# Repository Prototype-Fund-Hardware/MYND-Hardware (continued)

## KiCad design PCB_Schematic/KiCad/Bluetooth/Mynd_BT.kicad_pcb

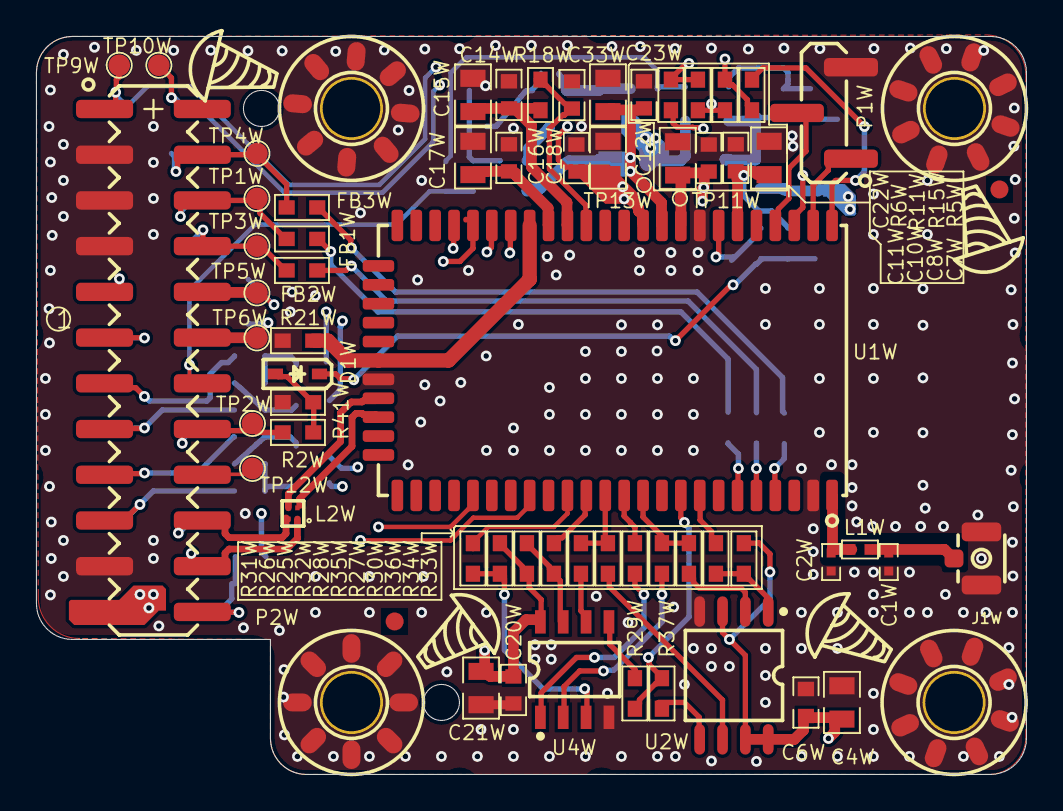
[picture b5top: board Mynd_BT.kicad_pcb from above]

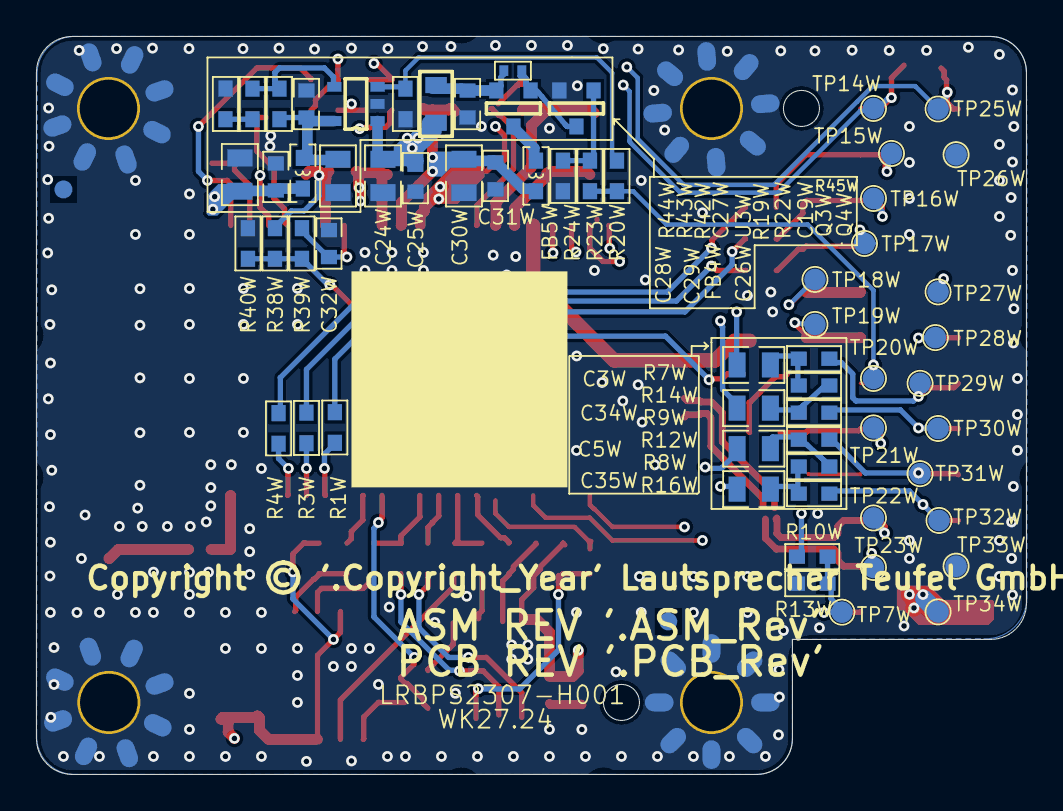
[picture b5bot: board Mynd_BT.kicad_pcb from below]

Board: 4 copper layers, 55.0 x 41.0 mm, 136 parts (66 on the bottom side), 79 nets.

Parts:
C1W, C2W: 0.5pF; C0402
C3W, C4W, C5W, C7W, C11W, C12W, C15W, C17W, C21W, C23W, C24W, C26W, C28W, C30W, C34W, C35W: 10uF; C0805_145
C6W, C8W, C10W, C14W, C16W, C18W, C19W, C20W, C22W, C25W, C27W, C29W, C31W: 100nF; C0603X100
C32W: 100pF; C0603X80
C33W: 1nF; C0603X100
D1W: 1N4148; SOD-323
FB1W, FB2W, FB3W: 0R; R0603
FB4W, FB5W: 600R; L0603
J1W: 9181-000030; I-PEX MHF
L1W: 0R; R0402
L2W: 90R; COM_CHOKE_SMD_ICMF062P
MH1W, MH2W, MH3W, MH4W: SCREW_HOLE; SCREW_D32
MK1W, MK2W: MARK
P1W: Header 3P PITCH=2.54mm SMT; Pin_Header_SMD_S_T_254_3P
P2W: Connector 2 x 12P 2.54mm SMT; Pin_Header_SMD_2X12_254
Q3W: CJ3401; SOT23-GSD
Q4W: 2N7002K; SOT23-GSD
R1W, R3W, R4W, R27W, R28W, R29W, R30W, R31W, R32W, R34W, R35W, R36W, R37W: 33R; R0603
R2W, R11W, R13W, R15W, R25W, R26W, R33W: 10k; R0603
R5W, R6W, R9W, R16W, R21W: 0R; R0603
R7W, R12W: 3.3k; R0603
R8W, R14W: 6.8k; R0603
R10W: 100k; R0603
R18W: 33k; R0603
R19W, R24W, R41W: 47k; R0603
R20W, R23W, R39W: 1k; R0603
R22W: 2.2R; R0805
R38W: 1M; R0603
R40W: 560k; R0603
R42W: 680k; R0603
R43W: 150k; R0603
R44W: 20k; R0603
R45W: 100k; R0402
TP1W, TP2W, TP3W, TP4W, TP5W, TP6W, TP7W, TP9W, TP10W, TP12W, TP14W, TP15W, TP16W, TP17W, TP18W, TP19W, TP20W, TP21W, TP22W, TP23W, TP25W, TP26W, TP27W, TP28W, TP29W, TP30W, TP31W, TP32W, TP33W, TP34W: TP12; TP120
TP11W, TP13W: TP06; TP060
Teufel_ASM_Label1W: =Comment/Name; Teufel_ASM_Rev
Teufel_Copyright1W: =Comment/Name; TEUFEL_COPYRIGHT
Teufel_PCB_Label1W: =Comment/Name; Teufel_PCB_Rev
Teufel_PCB_Logo1W: T.3.0.0040-3.1; Teufel_NoLogo
U1W: WB-2835P; BT_59P_L260XW150XH26_P105
U2W: RCI025064-B000; SO_8_200
U3W: SGM2036-ADJYN5G/TR; SOT23-5
U4W: APS6404L-3SQN; SO-8

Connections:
3V3_STB: P2W.11, R10W.1, TP28W.1
5V_CCPD: C24W.1, C25W.2, P2W.23, R22W.2, TP34W.1, U3W.1
AGND: R21W.2, U1W.30, U1W.43
BT_2_BCLK: FB1W.1, P2W.6, TP1W.1, TP16W.1
BT_2_LRCK: FB2W.1, P2W.8, TP3W.1, TP17W.1
BT_2_SDAT: FB3W.1, P2W.4, TP4W.1, TP15W.1
BT_AVCC: C16W.1, C17W.2, U1W.44
BT_Ctrl_Pwr: P2W.14, R20W.2, R23W.1, TP20W.1
BT_Ctrl_Vreg: P2W.18, TP12W.1
BT_RTCVDD: C7W.1, C8W.1, R38W.1, U1W.54
BT_SCL: P2W.2, R5W.1, R15W.2, TP10W.1, TP14W.1
BT_SDA: P2W.1, R6W.1, R11W.2, TP9W.1, TP25W.1
BT_SVCC: C14W.1, C15W.2, R18W.1, U1W.45
BT_VBAT: C10W.2, C11W.2, C28W.1, C29W.2, FB4W.2, TP11W.1, U1W.51
BT_VBUS: C22W.1, C23W.1, C30W.2, C31W.2, FB5W.2, TP13W.1, U1W.50
BT_VCC: C4W.2, C6W.2, C12W.2, C18W.2, C20W.1, C21W.1, R11W.1, R15W.1, R25W.1, R26W.1, R33W.1, U1W.49, U2W.3, U2W.7, U2W.8, U4W.8
BT_Ver: P2W.24, R10W.2, R13W.1, TP7W.1
BUD_N: L2W.4, U1W.28
BUD_P: L2W.3, U1W.27
FLASH_CS: R33W.2, R34W.2, U2W.1
FLASH_MISO: R36W.2, U2W.2
FLASH_MOSI: R37W.2, U2W.5
FLASH_SCLK: R35W.2, U2W.6
GND: C1W.2, C2W.2, C4W.1, C6W.1, C7W.2, C8W.2, C10W.1, C11W.1, C12W.1, C14W.2, C15W.1, C16W.2, C17W.1, C18W.1, C19W.2, C20W.2, C21W.2, C22W.2, C23W.2, C24W.2, C25W.1, C26W.2, C27W.1, C28W.2, C29W.1, C30W.1, C31W.1, C32W.1, C33W.1, J1W.2, MH1W.1, MH2W.1, MH3W.1, MH4W.1, P1W.3, P2W.3, P2W.5, P2W.7, P2W.21, Q4W.S, R13W.2, R19W.2, R21W.1, R24W.2, R40W.2, R41W.2, R44W.1, TP26W.1, TP33W.1, U1W.2, U1W.29, U1W.52, U2W.4, U3W.2, U4W.4
GPIO0: R5W.2, U1W.59
GPIO1: R6W.2, U1W.57
GPIO2/UART_RX: P1W.1, U1W.58
GPIO3/UART_TX: P1W.2, U1W.56
GPIO8: R27W.1, U1W.12
GPIO9: R28W.1, R35W.1, U1W.13
GPIO10: R30W.1, R36W.1, U1W.11
GPIO11: R29W.1, R37W.1, U1W.9
GPIO13: R32W.1, U1W.14
GPIO14: R31W.1, U1W.15
GPIO16: R34W.1, U1W.8
Line_L_N: P2W.15, R9W.2, TP30W.1
Line_L_P: P2W.13, R7W.2, TP29W.1
Line_R_N: P2W.19, R16W.2, TP32W.1
Line_R_P: P2W.17, R12W.2, TP31W.1
MCU_RX: P2W.10, TP5W.1, TP18W.1, U1W.20
MCU_TX: P2W.12, TP6W.1, TP19W.1, U1W.17
NetC1W_1: C1W.1, J1W.1, L1W.1
NetC2W_1: C2W.1, L1W.2, U1W.1
NetC3W_1: C3W.1, U1W.39
NetC3W_2: C3W.2, R7W.1, R14W.2
NetC5W_1: C5W.1, U1W.41
NetC5W_2: C5W.2, R8W.2, R12W.1
NetC19W_1: C19W.1, Q3W.S, R22W.1, R45W.1
NetC26W_1: C26W.1, C27W.2, FB4W.1, R42W.1, U3W.5
NetC32W_2: C32W.2, R39W.2, U1W.53
NetC33W_2: C33W.2, R18W.2, U1W.46
NetC34W_1: C34W.1, U1W.40
NetC34W_2: C34W.2, R9W.1, R14W.1
NetC35W_1: C35W.1, U1W.42
NetC35W_2: C35W.2, R8W.1, R16W.1
NetD1W_A: D1W.A, R2W.1, R41W.1
NetFB1W_2: FB1W.2, R1W.2
NetFB2W_2: FB2W.2, R3W.2
NetFB3W_2: FB3W.2, R4W.2
NetFB5W_1: FB5W.1, Q3W.D
NetQ3W_G: Q3W.G, Q4W.D, R45W.2
NetQ4W_G: Q4W.G, R23W.2, R24W.1
NetR1W_1: R1W.1, U1W.6
NetR3W_1: R3W.1, U1W.5
NetR4W_1: R4W.1, U1W.4
NetR19W_1: R19W.1, R20W.1, U3W.3
NetR42W_2: R42W.2, R43W.2, U3W.4
NetR43W_1: R43W.1, R44W.2
ON/OFF: D1W.K, R38W.2, R39W.1, R40W.1
PSRAM_CE: R27W.2, U4W.1
PSRAM_SCLK: R28W.2, U4W.6
PSRAM_SIO0: R29W.2, U4W.5
PSRAM_SIO1: R30W.2, U4W.2
PSRAM_SIO2: R26W.2, R31W.2, U4W.3
PSRAM_SIO3: R25W.2, R32W.2, U4W.7
USB_B_N: L2W.2, P2W.20, TP22W.1
USB_B_P: L2W.1, P2W.22, TP23W.1
VSys: P2W.9, TP27W.1
\BT_RST: P2W.16, R2W.2, TP2W.1, TP21W.1

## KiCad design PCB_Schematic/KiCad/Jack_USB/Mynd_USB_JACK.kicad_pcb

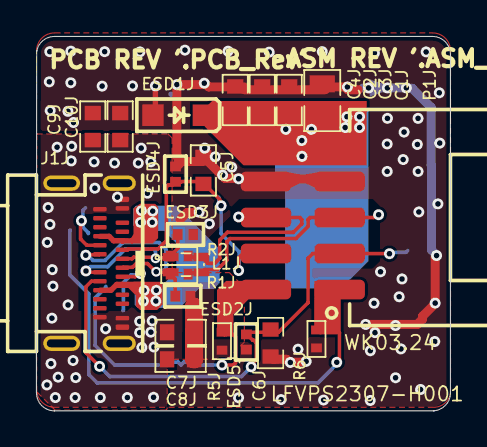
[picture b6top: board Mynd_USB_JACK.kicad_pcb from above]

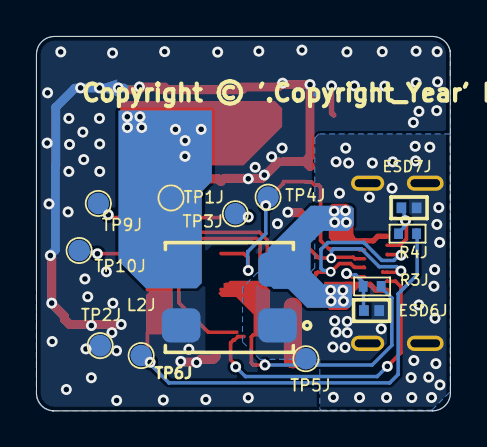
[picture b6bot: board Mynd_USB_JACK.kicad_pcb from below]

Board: 2 copper layers, 23.0 x 20.8 mm, 39 parts (14 on the bottom side), 14 nets.

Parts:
C1J: 2.2uF; C0805_145
C2J, C8J, C10J: 100nF; C0603X100
C3J, C4J: 10nF; C0603X100
C5J, C6J: 470pF; C0603X80
C7J, C9J: 1nF; C0603X100
ESD1J: SMF26AL; SOD-123FL
ESD2J, ESD3J, ESD4J, ESD5J, ESD6J, ESD7J: CESD0501CU; DFN2_100X60X50_65
J1J: NG-HC-0412; USB_TYPE_C_HC_0768
L1J: 90R; CET2012D
L2J: 700R; DU_IND_SMD_SCM7060
P1J: WB200AW-10; WB200AW_2x5P
R1J, R2J, R3J, R4J: 0R; R0402
R5J, R6J: NC; R0402
TP1J, TP2J, TP3J, TP4J, TP5J, TP6J, TP9J, TP10J: TP12; TP120
Teufel_ASM_Label1J: 3.2; Teufel_ASM_Rev
Teufel_Copyright1K: 2023; TEUFEL_COPYRIGHT
Teufel_PCB_Label1J: 3.2; Teufel_PCB_Rev
Teufel_PCB_Logo1K: T.3.0.0040-3.2; Teufel_NoLogo

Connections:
D2_1_N: ESD2J.2, J1J.A7, J1J.B7, L1J.2, R1J.1
D2_1_P: ESD3J.2, J1J.A6, J1J.B6, L1J.1, R2J.1
GND: C1J.2, C2J.2, C3J.2, C4J.2, C5J.2, C6J.2, C7J.2, C8J.2, C9J.2, C10J.2, ESD1J.A, ESD2J.1, ESD3J.1, ESD4J.2, ESD5J.2, L2J.4, P1J.7, P1J.8, R5J.1, R6J.1, TP2J.1
NetC7J_1: C7J.1, C8J.1, C9J.1, C10J.1, ESD6J.1, ESD7J.1, J1J.A1, J1J.A12, J1J.B1, J1J.B12, J1J.G1, J1J.G2, J1J.G3, J1J.G4, L2J.1
NetESD6J_2: ESD6J.2, J1J.A8, R3J.1
NetESD7J_2: ESD7J.2, J1J.B8, R4J.1
NetJ1J_A4: J1J.A4, J1J.A9, J1J.B4, J1J.B9, L2J.2
USB-CC1: C5J.1, ESD4J.1, J1J.A5, P1J.4, TP4J.1
USB-CC2: C6J.1, ESD5J.1, J1J.B5, P1J.3, TP10J.1
USB_J_N: L1J.3, P1J.5, R1J.2, TP9J.1
USB_J_P: L1J.4, P1J.6, R2J.2, TP3J.1
USB_SBU1: P1J.2, R3J.2, R5J.2, TP5J.1
USB_SBU2: P1J.1, R4J.2, R6J.2, TP6J.1
VBUS_C: C1J.1, C2J.1, C3J.1, C4J.1, ESD1J.K, L2J.3, P1J.9, P1J.10, TP1J.1

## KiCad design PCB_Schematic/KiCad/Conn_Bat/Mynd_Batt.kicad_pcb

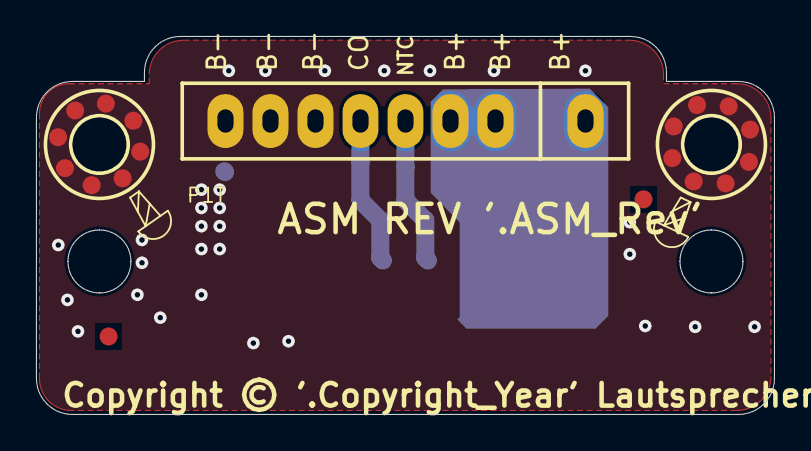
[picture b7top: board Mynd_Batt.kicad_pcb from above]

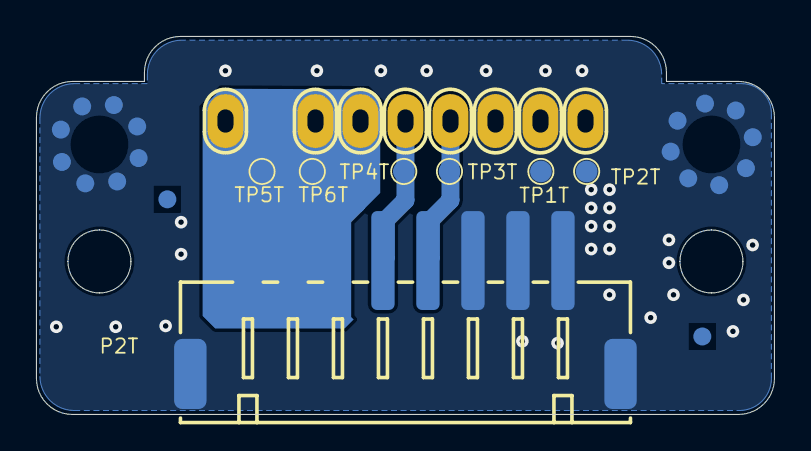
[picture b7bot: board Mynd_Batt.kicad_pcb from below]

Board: 2 copper layers, 41.0 x 21.0 mm, 15 parts (7 on the bottom side), 4 nets.

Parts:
MH1T, MH2T: SCREW_HOLE; SCREW_D30
MK1T, MK2T: MARK
P1T: 8P PITCH=2.5mm; TSB1_05282
P2T: WT250MW-084R-0W; CON_250_SMD_H_8P
TP1T, TP2T, TP3T, TP4T, TP5T, TP6T: TP12; TP120
Teufel_ASM_Label1T: 3.1; Teufel_ASM_Rev
Teufel_Copyright1T: 2023; TEUFEL_COPYRIGHT
Teufel_PCB_Logo1T: Teufel_NoLogo

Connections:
Bat+: P1T.1, P1T.2, P1T.3, P2T.6, P2T.7, P2T.8, TP5T.1, TP6T.1
Bat-: MH1T.1, MH2T.1, P1T.6, P1T.7, P1T.8, P2T.0, P2T.1, P2T.2, P2T.3, TP1T.1, TP2T.1
C_Open: P1T.5, P2T.4, TP3T.1
NTC: P1T.4, P2T.5, TP4T.1

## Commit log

2025-05-21 initial
